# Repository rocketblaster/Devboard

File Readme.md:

# Development Board

## Description
This is a 47x35mm development board PCB made with a bare bones ESP32-C3. It can support wireless connections which is useful. It contanis three pin headers, with one containing power supply gpio. The other one is GPIO only and lastly the 2 pins are for TXD and RXD. Uses USB-C to get power. Boot switch and reset switch helps to activate anything using the chip. Chip enable can be connected via pins.

There's a red power LED near USB-C. Blue and green located on top for testing LED on top for testing LED. The case features pinout labels.

## Case

## Demo Case

[3D case demo link](https://a360.co/3RtKpME)

## KiCanvas

[Demo Link](https://kicanvas.org/?repo=https%3A%2F%2Fgithub.com%2Frocketblaster%2FDevboard%2Ftree%2Fmain%2Fsrc%2Fkicad)

## Schematic

## PCB

## Render

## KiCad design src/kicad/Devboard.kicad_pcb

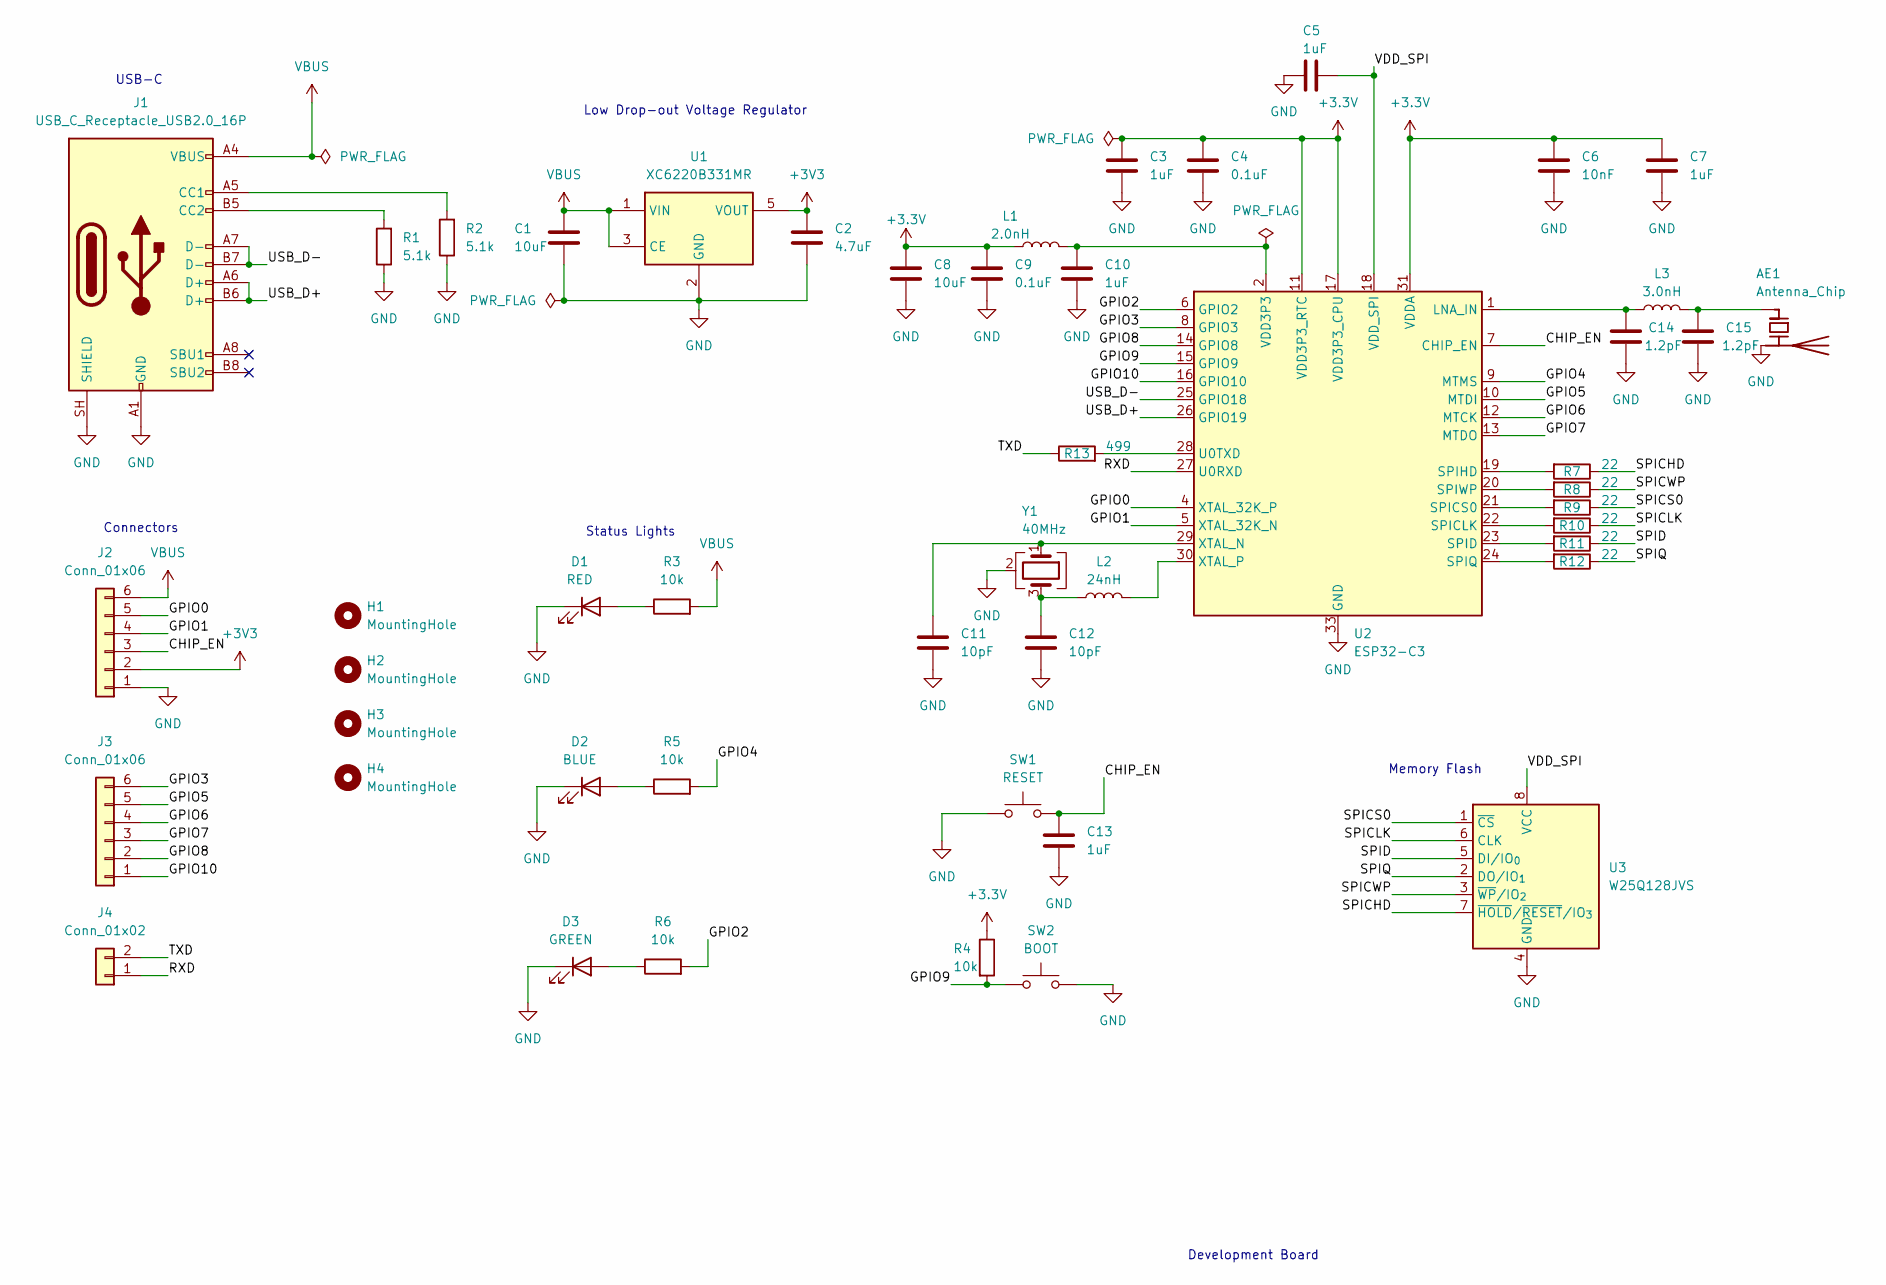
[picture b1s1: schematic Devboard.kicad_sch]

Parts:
AE1: Antenna_Chip; Johanson_2450AT18x100; LCSC Part C89334
C1, C8: 10uF; C_0603_1608Metric; LCSC Part C96446
C2: 4.7uF; C_0603_1608Metric; LCSC Part C69335
C3, C5, C7, C10, C13: 1uF; C_0402_1005Metric; LCSC Part C52923
C4, C9: 0.1uF; C_0402_1005Metric; LCSC Part C1525
C6: 10nF; C_0402_1005Metric; LCSC Part C15195
C11, C12: 10pF; C_0603_1608Metric; LCSC Part C1634
C14, C15: 1.2pF; C_0201_0603Metric; LCSC Part C85895
D1: RED; LED_0603_1608Metric; LCSC Part C19171390
D2: BLUE; LED_0603_1608Metric; LCSC Part C965807
D3: GREEN; LED_0603_1608Metric; LCSC Part C19273151
H1, H2, H3, H4: MountingHole; MountingHole_2.2mm_M2
J1: USB_C_Receptacle_USB2.0_16P; USB-C-SMD_TYPE-C-16PIN-2MD-073; LCSC Part C2765186
J2, J3: Conn_01x06; PinHeader_1x06_P2.54mm_Vertical
J4: Conn_01x02; PinHeader_1x02_P2.54mm_Vertical
L1: 2.0nH; L_0402_1005Metric; LCSC Part C18216
L2: 24nH; L_0402_1005Metric; LCSC Part C167472
L3: 3.0nH; L_0201_0603Metric; LCSC Part C98044
R1, R2: 5.1k; R_0603_1608Metric; LCSC Part C2907044
R3, R4, R5, R6: 10k; R_0603_1608Metric; LCSC Part C2930027
R7, R8, R9, R10, R11, R12: 22; R_0603_1608Metric; LCSC Part C2907129
R13: 499; R_0603_1608Metric; LCSC Part C23065
SW1: RESET; SW-SMD_L3.9-W3.0-P4.45; LCSC Part C720477
SW2: BOOT; SW-SMD_L3.9-W3.0-P4.45; LCSC Part C720477
U1: XC6220B331MR; SOT-23-5; LCSC Part C86534
U2: ESP32-C3; QFN-32-1EP_5x5mm_P0.5mm_EP3.7x3.7mm; LCSC Part C2838500
U3: W25Q128JVS; SOIC-8_5.3x5.3mm_P1.27mm; LCSC Part C97521
Y1: 40MHz; Crystal_SMD_3225-4Pin_3.2x2.5mm; LCSC Part C5444549

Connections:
+3.3V: C3.1, C4.1, C6.1, C7.1, C8.1, C9.1, L1.1, R4.1, U2.11 (VDD3P3_RTC), U2.17 (VDD3P3_CPU), U2.31 (VDDA), U2.32 (VDDA)
+3V3: C2.1, J2.2, U1.5 (VOUT)
/CHIP_EN: C13.1, J2.3, SW1.2, U2.7 (CHIP_EN)
/GPIO0: J2.5, U2.4 (XTAL_32K_P)
/GPIO1: J2.4, U2.5 (XTAL_32K_N)
/GPIO2: R6.2, U2.6 (GPIO2)
/GPIO3: J3.6, U2.8 (GPIO3)
/GPIO4: R5.2, U2.9 (MTMS)
/GPIO5: J3.5, U2.10 (MTDI)
/GPIO6: J3.4, U2.12 (MTCK)
/GPIO7: J3.3, U2.13 (MTDO)
/GPIO8: J3.2, U2.14 (GPIO8)
/GPIO9: R4.2, SW2.1, U2.15 (GPIO9)
/GPIO10: J3.1, U2.16 (GPIO10)
/RXD: J4.1, U2.27 (U0RXD)
/SPICHD: R7.1, U3.7 (~HOLD/~RESET/IO_{3})
/SPICLK: R10.1, U3.6 (CLK)
/SPICS0: R9.1, U3.1 (~CS)
/SPICWP: R8.1, U3.3 (~WP/IO_{2})
/SPID: R11.1, U3.5 (DI/IO_{0})
/SPIQ: R12.1, U3.2 (DO/IO_{1})
/TXD: J4.2, R13.1
/USB_D+: J1.A6 (D+), J1.B6 (D+), U2.26 (GPIO19)
/USB_D-: J1.A7 (D-), J1.B7 (D-), U2.25 (GPIO18)
/VDD_SPI: C5.2, U2.18 (VDD_SPI), U3.8 (VCC)
GND: AE1.2 (PCB_Trace), C1.2, C2.2, C3.2, C4.2, C5.1, C6.2, C7.2, C8.2, C9.2, C10.2, C11.2, C12.2, C13.2, C14.1, C15.1, D1.1 (K), D2.1 (K), D3.1 (K), J1.A1 (GND), J1.A12 (GND), J1.B1 (GND), J1.B12 (GND), J1.SH (SHIELD), J2.1, R1.1, R2.1, SW1.1, SW2.2, U1.2 (GND), U2.33 (GND), U3.4 (GND), Y1.2 (G), Y1.4 (G)
unnamed: AE1.1 (FEED), C15.2, L3.2
unnamed: C10.1, L1.2, U2.2 (VDD3P3), U2.3 (VDD3P3)
unnamed: C12.1, L2.1, Y1.3
unnamed: D1.2 (A), R3.1
unnamed: D2.2 (A), R5.1
unnamed: D3.2 (A), R6.1
unnamed: J1.A5 (CC1), R2.2
unnamed: J1.B5 (CC2), R1.2
unnamed: C14.2, L3.1, U2.1 (LNA_IN)
unnamed: R10.2, U2.22 (SPICLK)
unnamed: R9.2, U2.21 (SPICS0)
unnamed: R11.2, U2.23 (SPID)
unnamed: R7.2, U2.19 (SPIHD)
unnamed: R12.2, U2.24 (SPIQ)
unnamed: R8.2, U2.20 (SPIWP)
unnamed: R13.2, U2.28 (U0TXD)
unnamed: C11.1, U2.29 (XTAL_N), Y1.1
unnamed: L2.2, U2.30 (XTAL_P)
VBUS: C1.1, J1.A4 (VBUS), J1.A9 (VBUS), J1.B4 (VBUS), J1.B9 (VBUS), J2.6, R3.2, U1.1 (VIN), U1.3 (CE)

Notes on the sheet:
Low Drop-out Voltage Regulator
USB-C
Connectors
Development Board
Memory Flash
Status Lights

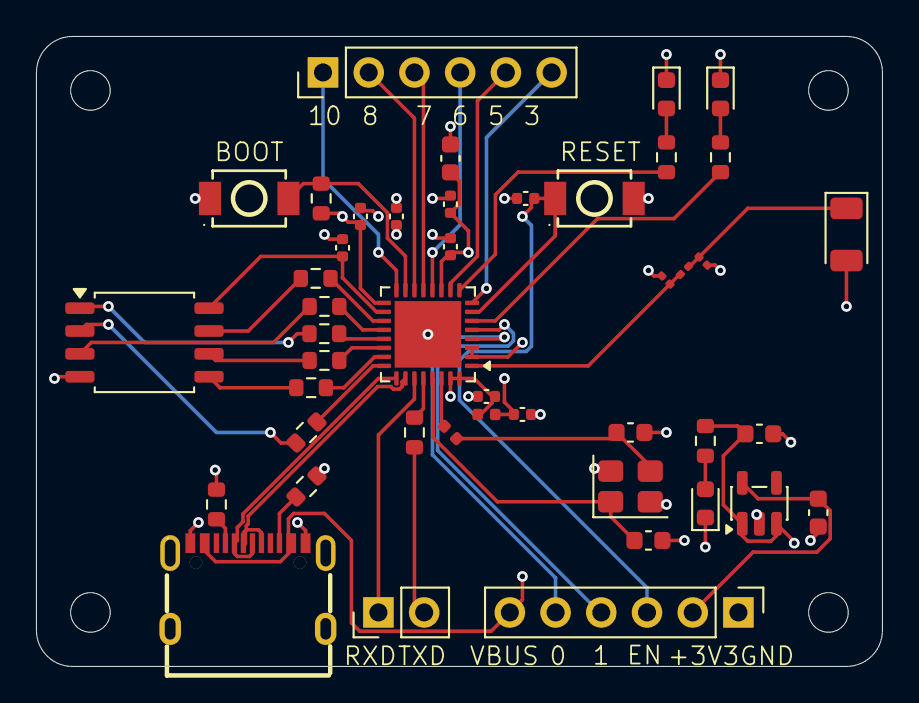
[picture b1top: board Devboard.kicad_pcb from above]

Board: 4 copper layers, 47.0 x 35.0 mm, 49 parts (0 on the bottom side), 45 nets.

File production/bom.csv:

Designator,Footprint,Quantity,Value,LCSC Part #
AE1,Johanson_2450AT18x100,1,Antenna_Chip,C89334
"C1, C8",0603,2,10uF,C96446
"C10, C13, C3, C5, C7",0402,5,1uF,C52923
"C11, C12",0603,2,10pF,C1634
"C14, C15",0201,2,1.2pF,C85895
C2,0603,1,4.7uF,C69335
"C4, C9",0402,2,0.1uF,C1525
C6,0402,1,10nF,C15195
D1,0603,1,RED,C19171390
D2,0603,1,BLUE,C965807
D3,0603,1,GREEN,C19273151
J1,USB-C-SMD_TYPE-C-16PIN-2MD-073,1,USB_C_Receptacle_USB2.0_16P,C2765186
L1,0402,1,2.0nH,C18216
L2,0402,1,24nH,C167472
L3,0201,1,3.0nH,C98044
"R1, R2",0603,2,5.1k,C2907044
"R10, R11, R12, R7, R8, R9",0603,6,22,C2907129
R13,0603,1,499,C23065
"R3, R4, R5, R6",0603,4,10k,C2930027
SW1,SW-SMD_L3.9-W3.0-P4.45,1,RESET,C720477
SW2,SW-SMD_L3.9-W3.0-P4.45,1,BOOT,C720477
U1,SOT-23-5,1,XC6220B331MR,C86534
U2,QFN-32-1EP_5x5mm_P0.5mm_EP3.7x3.7mm,1,ESP32-C3,C2838500
U3,SOIC-8_5.3x5.3mm_P1.27mm,1,W25Q128JVS,C97521
Y1,Crystal_SMD_3225-4Pin_3.2x2.5mm,1,40MHz,C5444549

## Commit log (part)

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2026-05-10 Upload files
2026-05-11 small mistake
2026-05-11 Update journal
2026-05-12 New entry
2026-05-16 Updated Journal
2026-05-20 Update project
2026-05-20 Add Kicanvas link
2026-05-20 Update read me
2026-05-23 Update Journal after review
2026-05-23 Update hours
2026-05-23 Update total hours
2026-05-26 Add case
